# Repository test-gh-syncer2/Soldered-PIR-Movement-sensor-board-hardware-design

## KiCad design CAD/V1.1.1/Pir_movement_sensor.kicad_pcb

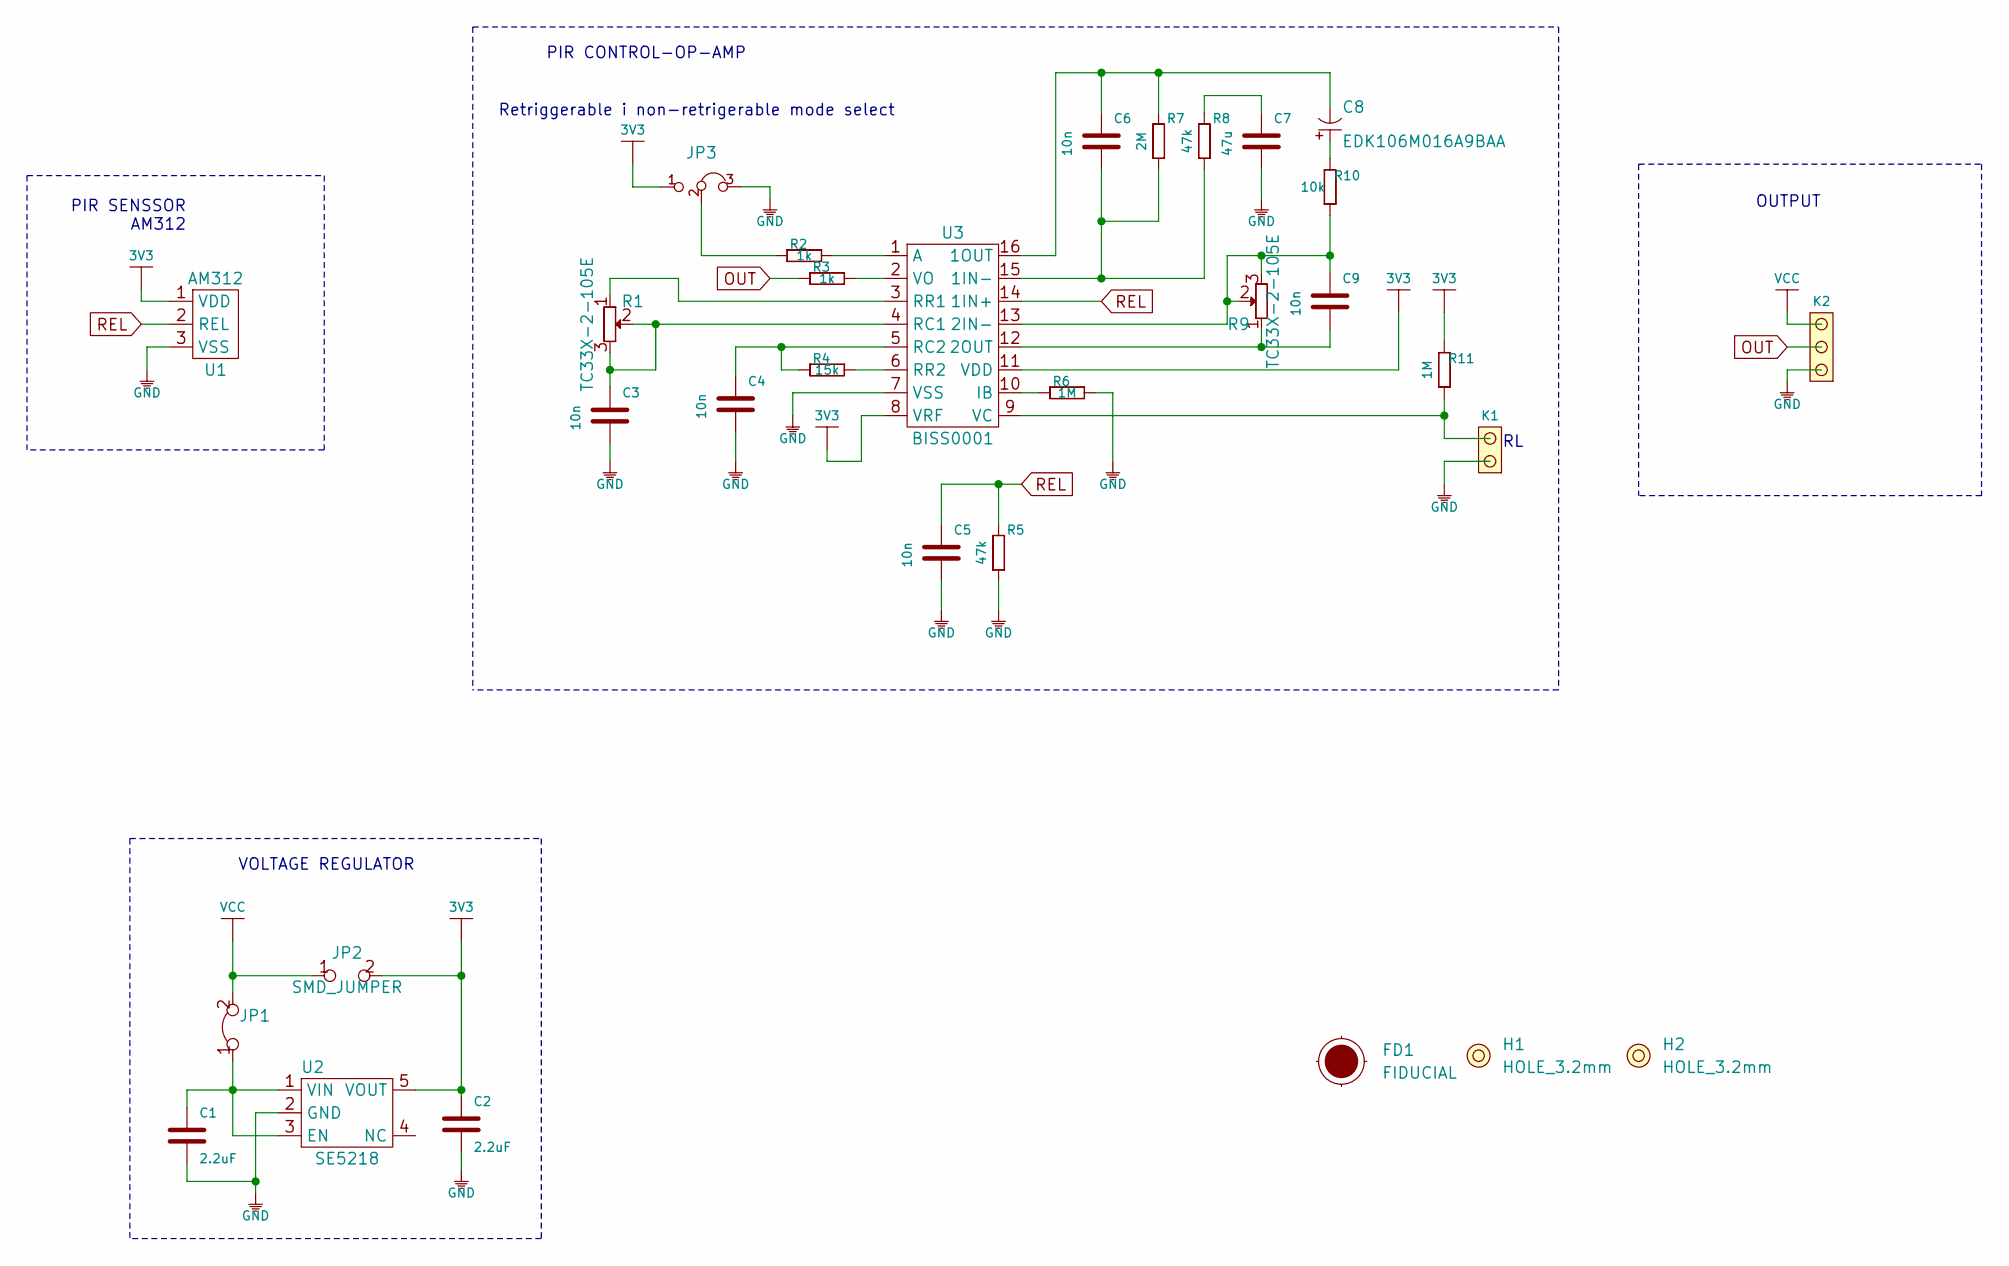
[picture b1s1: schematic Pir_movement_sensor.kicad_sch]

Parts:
C1, C2: 2.2uF; 0603C
C3, C4, C5, C6, C9: 10n; 0603C
C7: 47u; 0603C
C8: EDK106M016A9BAA; ELECTROLITIC_CAP_4mm
FD1: FIDUCIAL; FIDUCIAL_23
H1, H2: HOLE_3.2mm
JP1: SMD-JUMPER-CONNECTED_TRACE_SLODERMASK
JP2: SMD_JUMPER
JP3: SMD_JUMPER_3_PAD_CONNECTED_RIGHT
K1: HEADER_MALE_2X1
K2: HEADER_MALE_3X1
R1, R9: TC33X-2-105E; tc33x-2-103e
R2, R3: 1k; 0603R
R4: 15k; 0603R
R5, R8: 47k; 0603R
R6, R11: 1M; 0603R
R7: 2M; 0603R
R10: 10k; 0603R
U1: AM312; PIR_senzor
U2: SE5218; SOT-23-5
U3: BISS0001; SOP-16

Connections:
3V3: C2.2, JP2.2, JP3.1, R11.2, U1.1 (VDD), U2.5 (VOUT), U3.8 (VRF), U3.11 (VDD)
GND: C1.1, C2.1, C3.1, C4.1, C5.1, C7.1, JP3.3, K1.1, K2.1, R5.1, R6.2, U1.3 (VSS), U2.2 (GND), U3.7 (VSS)
unnamed: C1.2, JP1.1, U2.1 (VIN), U2.3 (EN)
unnamed: C3.2, R1.2, R1.3, U3.4 (RC1)
unnamed: C4.2, R4.1, U3.5 (RC2)
unnamed: C6.1, R7.1, R8.1, U3.15 (1IN-)
unnamed: C6.2, C8.2 (-), R7.2, U3.16 (1OUT)
unnamed: C7.2, R8.2
unnamed: C8.1 (+), R10.2
unnamed: C9.1, R9.1, U3.12 (2OUT)
unnamed: C9.2, R9.2, R9.3, R10.1, U3.13 (2IN-)
unnamed: JP3.2, R2.1
unnamed: K1.2, R11.1, U3.9 (VC)
unnamed: R1.1, U3.3 (RR1)
unnamed: R2.2, U3.1 (A)
unnamed: R3.2, U3.2 (VO)
unnamed: R4.2, U3.6 (RR2)
unnamed: R6.1, U3.10 (IB)
OUT: K2.2, R3.1
REL: C5.2, R5.2, U1.2 (REL), U3.14 (1IN+)
VCC: JP1.2, JP2.1, K2.3

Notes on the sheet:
PIR SENSSOR AM312
VOLTAGE REGULATOR
PIR CONTROL-OP-AMP
Retriggerable i non-retrigerable mode select
OUTPUT

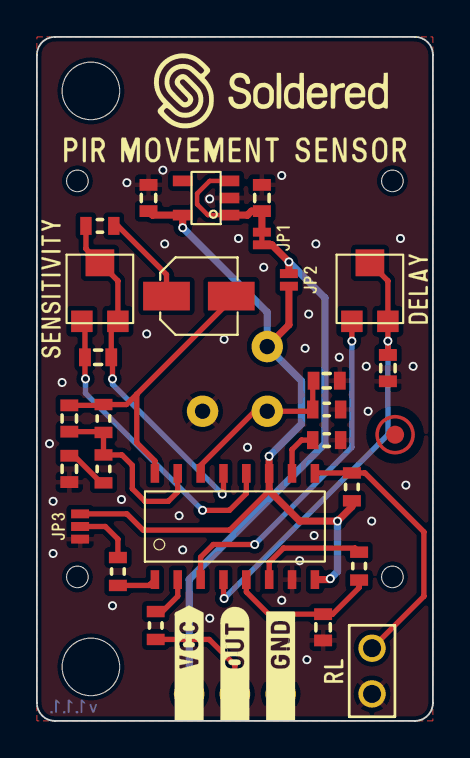
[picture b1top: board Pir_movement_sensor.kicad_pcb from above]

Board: 2 copper layers, 22.0 x 38.0 mm, 35 parts (1 on the bottom side), 21 nets.

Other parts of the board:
HOLE_L1, HOLE_L2, HOLE_L3, HOLE_L4: (no value)

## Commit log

2021-09-23 Syncing to git
2021-09-23 Updating open source files.
